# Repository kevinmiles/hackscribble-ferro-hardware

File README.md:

Hackscribble FRAM Hardware
==========================

#### *PCB designs for connecting Fujitsu MB85RS Ferroelectric memory (FRAM) to Arduino and LPCXpresso boards.*

Created on 20 April 2014 by Ray Benitez  
Last modified on 1 December 2014 by Ray Benitez		
  
These hardware designs are licensed by Ray Benitez under the Creative Commons Attribution-Sharealike 4.0 International License.
	
git@hackscribble.com | http://www.hackscribble.com | http://www.twitter.com/hackscribble

### About the hardware

#### Level converter circuits

These circuit snippets connect 3.3V MB85RS FRAM chips to 5V Arduino inputs / outputs.  

Two design approaches are shown:

1. Discrete design using BSS108 FETs, following the approach used by the Adafruit level converter.

2. Integrated design using TXB0104 to reduce PCB space required. 

The designs are in Eagle format.

#### Mini-shield

The mini-shield allows up to three 3.3V FRAMS to be connected to an Arduino (or an LPCXPresso board).  It uses an extended version of the integrated circuit snippet (above) using a TXB0108. The board has been tested with Arduino Uno and LPCXpresso 11U68 boards.

The design is in KiCad format.

The supply voltage for the Arduino / LPCXpresso side of the level converter is taken from the IOREF output of the Arduino / LPCXpresso.  This automatically adjusts for 3.3V or 5V boards.

The REVISION B board also includes test points for monitoring the SPI bus.
<br>

<hr>

### Change history

#### 1 December 2014

Added mini-shield REVISION C "slim" version.

#### 5 November 2014

Upgraded mini-shield to REVISION B.

#### 1 November 2014

Added mini-shield REVISION A.

#### 20 April 2014

Initial release of level converter circuits REVISION A.

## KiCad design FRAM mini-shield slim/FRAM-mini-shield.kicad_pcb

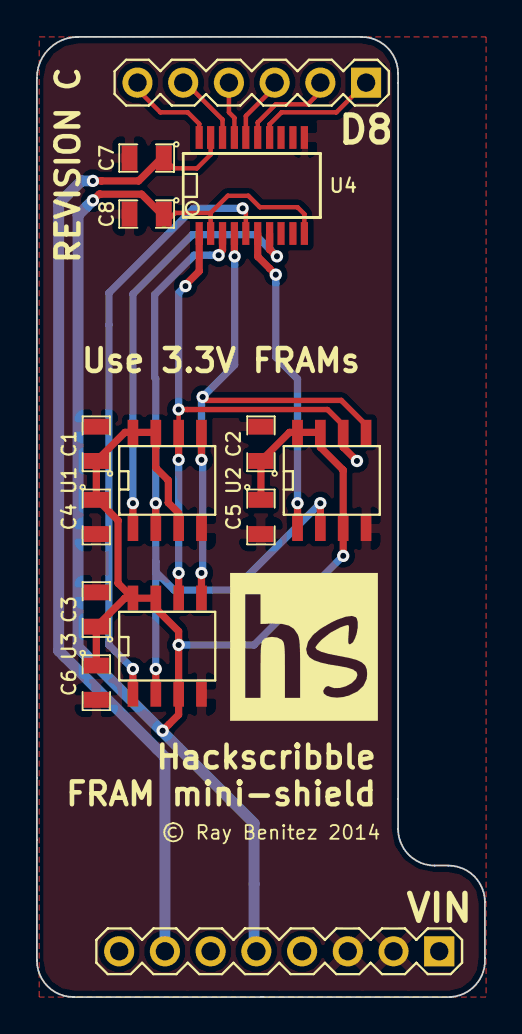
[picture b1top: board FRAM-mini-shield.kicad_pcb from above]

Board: 2 copper layers, 24.9 x 53.3 mm, 14 parts (0 on the bottom side), 15 nets.

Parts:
C1, C2, C3, C7, C8: 100nF; SMD-0805
C4, C5, C6: 10uF; SMD-0805
HDR1: AB2_HDR08-1; AB2_HDR_M08-1V
HDR2: AB2_HDR06-1; AB2_HDR_M06-1V
U1, U2, U3: MB85RS1MT; SOIC-8-W
U4: TXB0108; SSOP-20

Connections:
+3.3V: C1.1, C2.1, C3.1, C4.1, C5.1, C6.1, C8.1, HDR1.5, U1.3, U1.7, U1.8, U2.3, U2.7, U2.8, U3.3, U3.7, U3.8, U4.2, U4.10
GND: C1.2, C2.2, C3.2, C4.2, C5.2, C6.2, C7.2, C8.2, HDR1.2, HDR1.3, U1.4, U2.4, U3.4, U4.11
unnamed: C7.1, HDR1.7, U4.19
unnamed: HDR2.1, U4.14
unnamed: HDR2.2, U4.15
unnamed: HDR2.3, U4.16
unnamed: HDR2.4, U4.17
unnamed: HDR2.5, U4.18
unnamed: HDR2.6, U4.20
unnamed: U1.1, U4.7
unnamed: U1.2, U2.2, U3.2, U4.3
unnamed: U1.5, U2.5, U3.5, U4.4
unnamed: U1.6, U2.6, U3.6, U4.1
unnamed: U2.1, U4.6
unnamed: U3.1, U4.5

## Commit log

2014-04-28 Revision A.
2014-04-28 Creating first version of gh-pages.
2014-04-28 Adding content for Revision A.
2014-11-01 2014-11-01 release.
2014-11-01 Working on updates for mini-shield.
2014-11-01 Updated for release of mini-shield.
2014-11-05 2014-11-05 release.
2014-11-05 Updated README for 2014-11-05 release.
2014-11-05 Updated.
2014-12-02 2014-12-02 release.
2014-12-02 Updated for 2014-12-02 release.

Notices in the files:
FRAM mini-shield slim/FRAM-mini-shield.kicad_pcb:
© Ray Benitez 2014
